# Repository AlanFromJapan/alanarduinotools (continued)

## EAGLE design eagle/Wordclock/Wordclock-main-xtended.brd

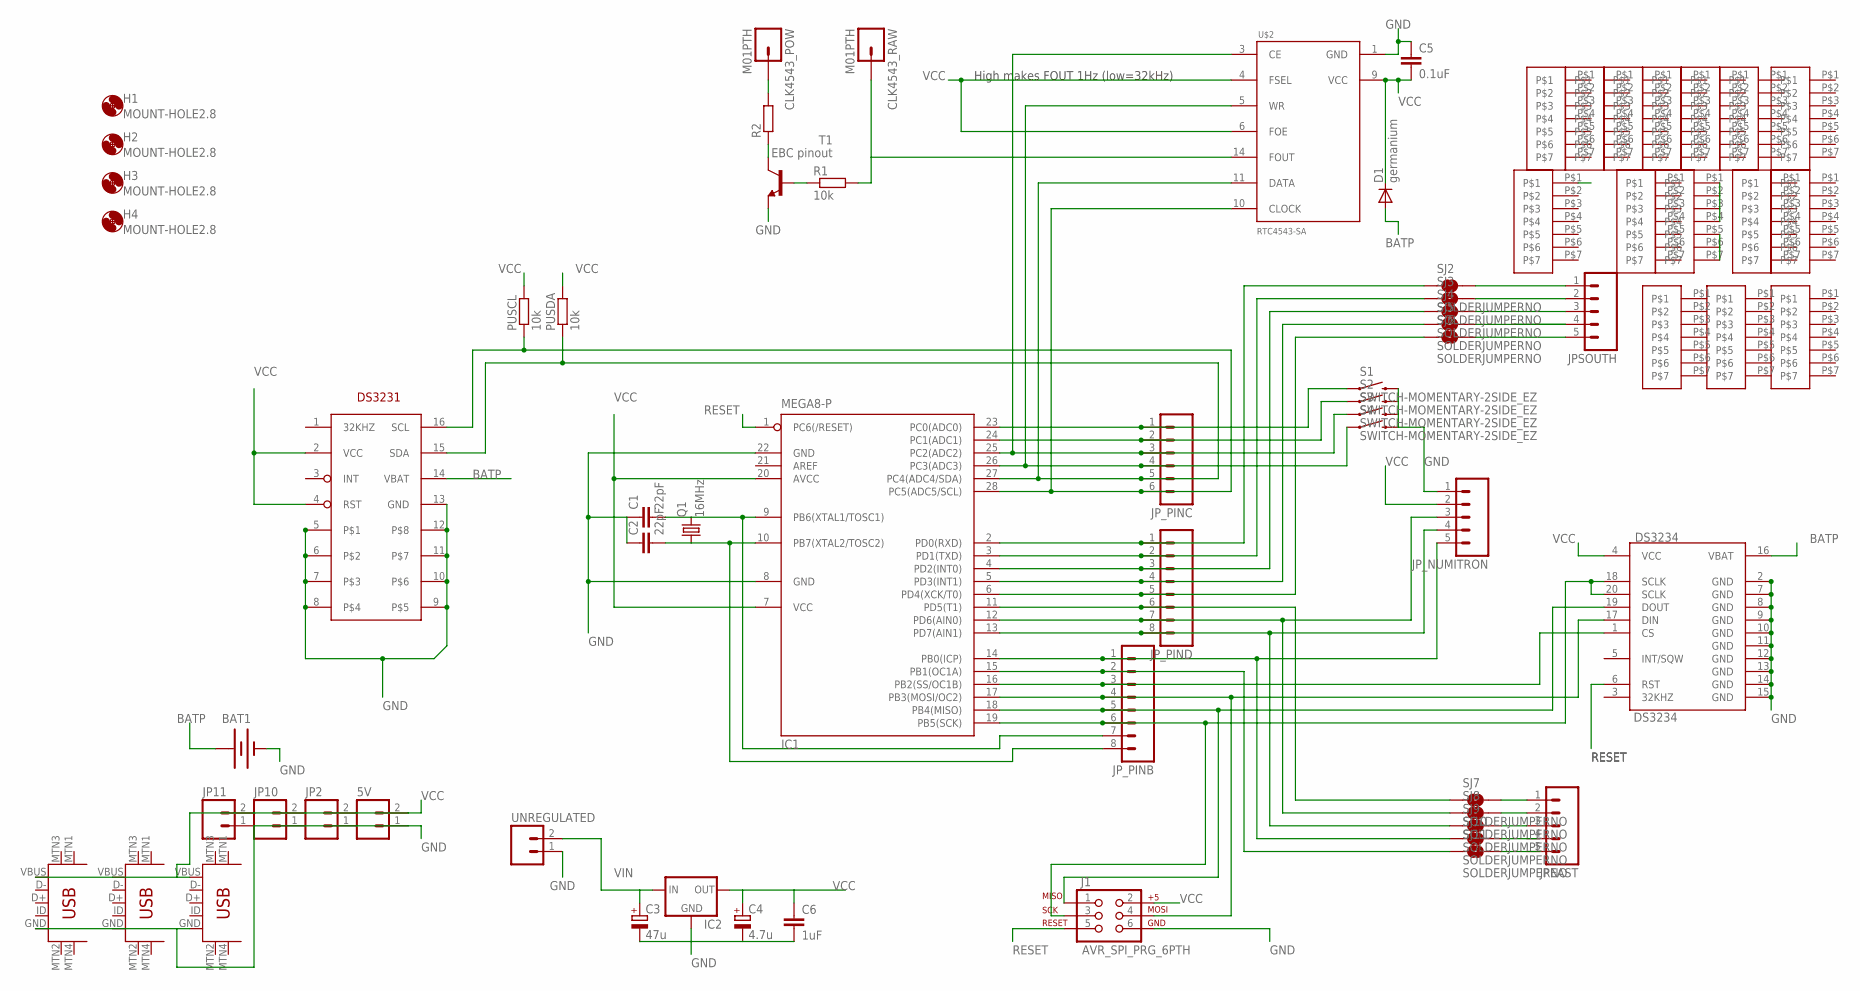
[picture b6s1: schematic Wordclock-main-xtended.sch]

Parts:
5V: M02PTH; 1X02
BAT1: BATTERY20PTH; BATTCOM_20MM_PTH
C1, C2: 22pF; C025-024X044
C3: 47u; E2,5-6E
C4: 4.7u; E2,5-6E
C5: 0.1uF; C025-024X044
C6: 1uF; C025-024X044
CLK4543_POW, CLK4543_RAW: M01PTH; 1X01
D1: germanium; D-7.5
DS3234: DS3234
H1, H2, H3, H4: MOUNT-HOLE2.8; 2,8
IC1: MEGA8-P; DIL28-3
IC2: V_REG_78XXSIDE; 78XXL
J1: AVR_SPI_PRG_6PTH; 2X3
JP1, JP3, JP4, JP5, JP6, JP7, JP8, JP9: M7_NOSILK
JP2: M02PTH; 1X02
JP10, JP11: M02PTH3; 1X02_LONGPADS
JPEAST: M05PTH; 1X05
JPSOUTH: M05PTH; 1X05
JP_NUMITRON: M05PTH; 1X05
JP_PINB: M081X08; 1X08
JP_PINC: M06SIP; 1X06
JP_PIND: M081X08; 1X08
PUSCL: 10k; 0204/5
PUSDA: 10k; 0204/5
Q1: 16MHz; HC49/S
R1: 10k; 0204/5
R2: R-EU_0204/5; 0204/5
S1, S2, S3, S4: SWITCH-MOMENTARY-2SIDE_EZ; TACTILE-PTH-SIDEEZ
SJ2, SJ3, SJ4, SJ5, SJ6, SJ7, SJ8, SJ9, SJ10, SJ11: SOLDERJUMPERNO; SJ_2S-NO
T1: EBC pinout; TO92-EBC
U$1: DS3231DS3231-SO16W; SO16W
U$2: RTC4543-SA; SOP14
U$3, U$4, U$5, U$6, U$8, U$9, U$10: M7_NOSILK
U$7, U$11, U$12: USB-MINIB-5PIN; USB-MINIB
UNREGULATED: M02PTH3; 1X02_LONGPADS

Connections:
BATP: BAT1.1 (+), D1.A, DS3234.16 (VBAT), U$1.14 (VBAT)
GND: 5V.1, BAT1.2 (-), C1.1, C2.1, C3.-, C4.-, C5.1, C6.2, DS3234.2 (GND), DS3234.7 (GND), DS3234.8 (GND), DS3234.9 (GND), DS3234.10 (GND), DS3234.11 (GND), DS3234.12 (GND), DS3234.13 (GND), DS3234.14 (GND), DS3234.15 (GND), IC1.8 (GND), IC1.22 (GND), IC2.GND, J1.6, JP2.1, JP10.1, JP11.1, JP_NUMITRON.1, S1.2, S2.2, S3.2, S4.2, T1.E, U$1.5, U$1.6, U$1.7, U$1.8, U$1.9, U$1.10, U$1.11, U$1.12, U$1.13 (GND), U$2.1 (GND), U$7.GND, U$8.P$1, U$8.P$2, U$8.P$3, U$8.P$4, U$11.GND, U$12.GND, UNREGULATED.1
unnamed: IC1.23 (PC0(ADC0)), JP_PINC.1, S1.1
unnamed: IC1.24 (PC1(ADC1)), JP_PINC.2, S2.1
unnamed: JPEAST.1, SJ7.2
unnamed: C1.2, IC1.9 (PB6(XTAL1/TOSC1)), JP_PINB.7, Q1.2
unnamed: C2.2, IC1.10 (PB7(XTAL2/TOSC2)), JP_PINB.8, Q1.1
unnamed: DS3234.1 (CS), IC1.16 (PB2(SS/OC1B)), JP_PINB.3
unnamed: IC1.25 (PC2(ADC2)), JP_PINC.3, S3.1, U$2.3 (CE)
unnamed: JPEAST.2, SJ8.2
unnamed: JPEAST.3, SJ9.2
unnamed: JPEAST.4, SJ10.2
unnamed: JPEAST.5, SJ11.2
unnamed: DS3234.18 (SCLK), DS3234.20 (SCLK), IC1.19 (PB5(SCK)), J1.3, JP_PINB.6
unnamed: DS3234.19 (DOUT), IC1.18 (PB4(MISO)), J1.1, JP_PINB.5
unnamed: DS3234.17 (DIN), IC1.17 (PB3(MOSI/OC2)), J1.4, JP_PINB.4
unnamed: JPSOUTH.1, SJ2.2
unnamed: JPSOUTH.2, SJ3.2
unnamed: JPSOUTH.3, SJ4.2
unnamed: JPSOUTH.4, SJ5.2
unnamed: JPSOUTH.5, SJ6.2
unnamed: IC1.2 (PD0(RXD)), JP_PIND.1, SJ2.1
unnamed: IC1.3 (PD1(TXD)), JP_PIND.2, SJ3.1
unnamed: IC1.4 (PD2(INT0)), JP_PIND.3, SJ4.1
unnamed: IC1.5 (PD3(INT1)), JP_PIND.4, SJ5.1
unnamed: IC1.6 (PD4(XCK/T0)), JP_PIND.5, SJ6.1
unnamed: IC1.15 (PB1(OC1A)), JP_PINB.2, SJ11.1
unnamed: IC1.14 (PB0(ICP)), JP_NUMITRON.5, JP_PINB.1, SJ10.1
unnamed: IC1.13 (PD7(AIN1)), JP_NUMITRON.4, JP_PIND.8, SJ9.1
unnamed: IC1.12 (PD6(AIN0)), JP_NUMITRON.3, JP_PIND.7, SJ8.1
unnamed: IC1.11 (PD5(T1)), JP_PIND.6, SJ7.1
unnamed: IC1.28 (PC5(ADC5/SCL)), JP_PINC.6, PUSCL.1, U$1.16 (SCL), U$2.10 (CLOCK)
unnamed: IC1.27 (PC4(ADC4/SDA)), JP_PINC.5, PUSDA.1, U$1.15 (SDA), U$2.11 (DATA)
unnamed: IC1.26 (PC3(ADC3)), JP_PINC.4, S4.1, U$2.5 (WR)
unnamed: CLK4543_RAW.1, R1.2, U$2.14 (FOUT)
unnamed: R1.1, T1.B
unnamed: R2.1, T1.C
unnamed: CLK4543_POW.1, R2.2
RESET: DS3234.6 (RST), IC1.1 (PC6(/RESET)), J1.5
VCC: 5V.2, C4.+, C5.2, C6.1, D1.C, DS3234.4 (VCC), IC1.7 (VCC), IC1.20 (AVCC), IC2.OUT, J1.2, JP2.2, JP10.2, JP11.2, JP_NUMITRON.2, PUSCL.2, PUSDA.2, U$1.2 (VCC), U$1.4 (RST), U$2.4 (FSEL), U$2.6 (FOE), U$2.9 (VCC), U$7.VBUS, U$8.P$5, U$8.P$6, U$8.P$7, U$10.P$1, U$11.VBUS, U$12.VBUS
VIN: C3.+, IC2.IN, UNREGULATED.2

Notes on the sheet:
High makes FOUT 1Hz (low=32kHz)

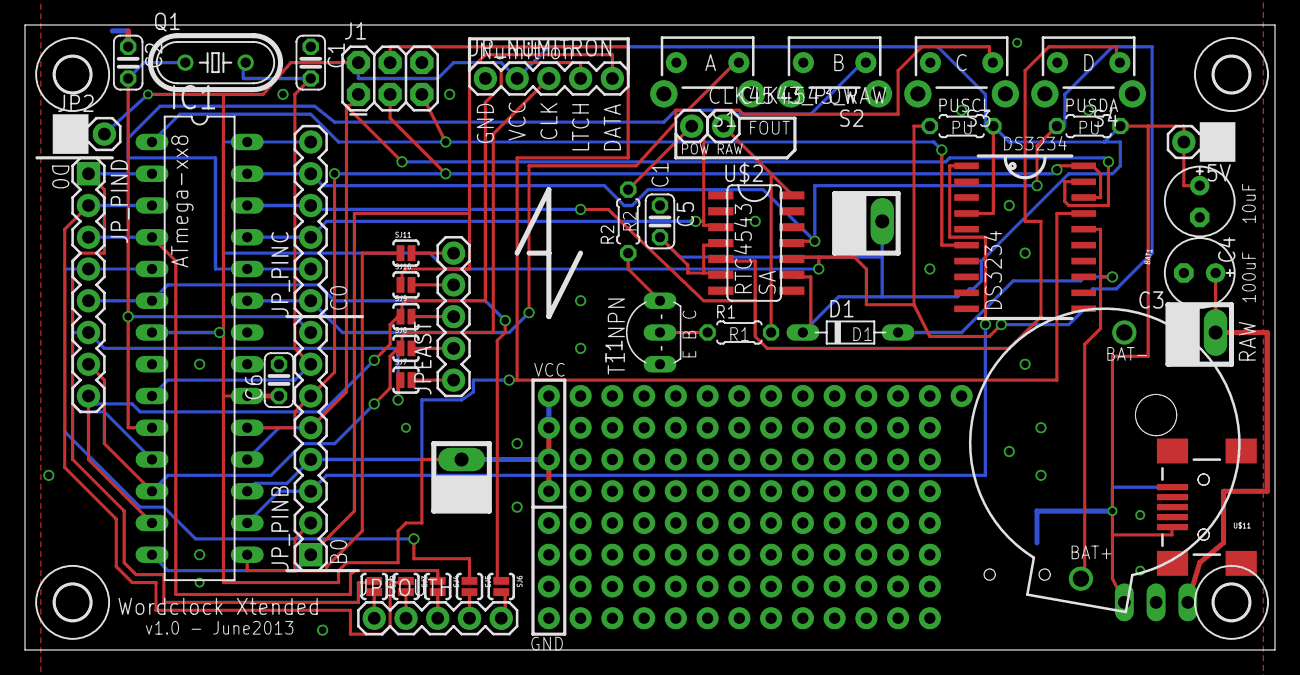
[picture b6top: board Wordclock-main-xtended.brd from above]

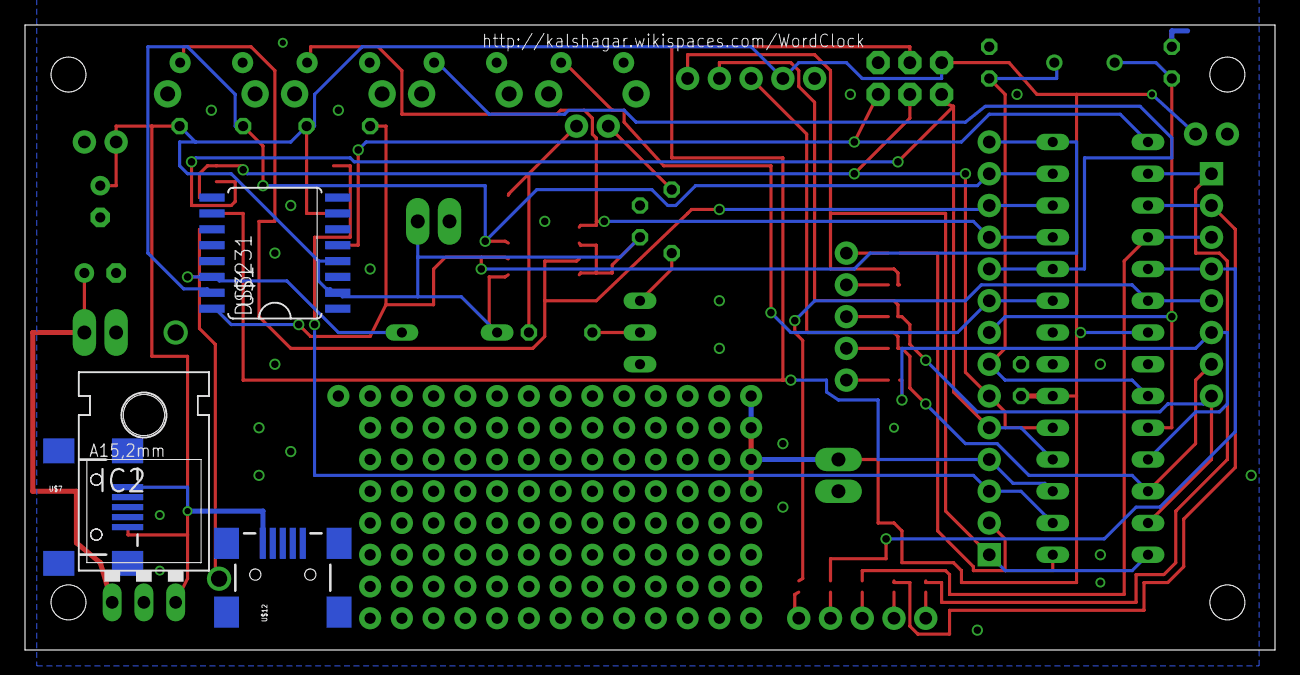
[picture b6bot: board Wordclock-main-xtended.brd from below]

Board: 2 copper layers, 100.0 x 50.0 mm, 69 parts (4 on the bottom side), 41 nets.

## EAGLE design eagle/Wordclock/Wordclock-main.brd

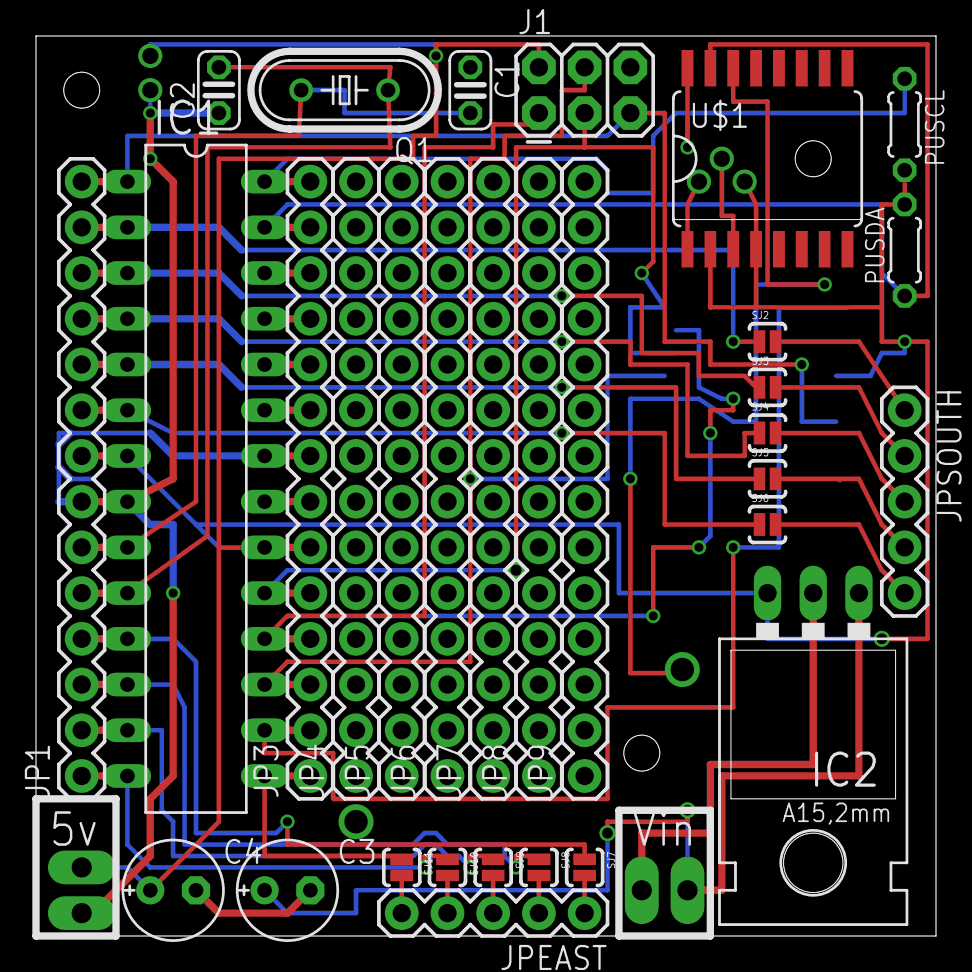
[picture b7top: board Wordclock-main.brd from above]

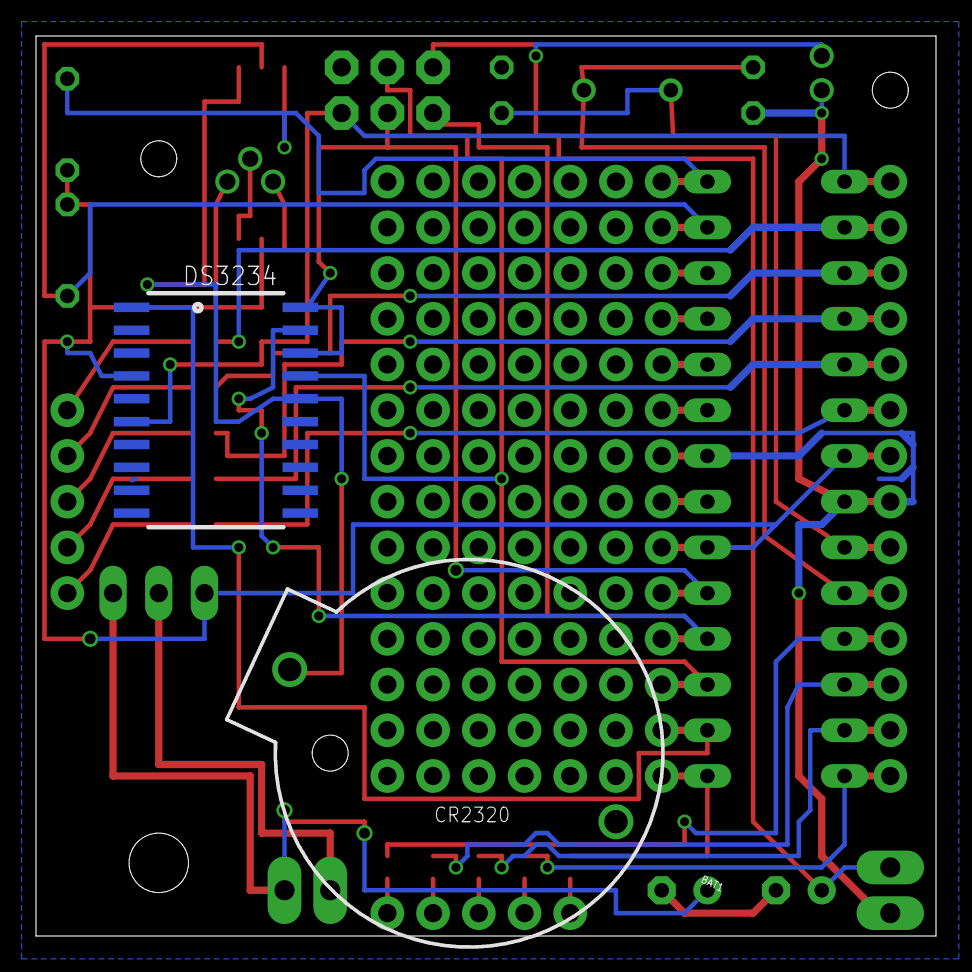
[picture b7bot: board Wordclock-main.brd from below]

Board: 2 copper layers, 50.0 x 50.0 mm, 35 parts (2 on the bottom side), 43 nets.

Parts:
5V: 1X02_LONGPADS
BAT1: BATTCOM_20MM_PTH
C1, C2: 22pF; C025-024X044
C3: 47u; E2,5-6E
C4: 4.7u; E2,5-6E
DS3234: DS3234
IC1: MEGA8-P; DIL28-3
IC2: 78XXL
J1: AVR_SPI_PRG_6PTH; 2X3
JP1, JP3, JP4, JP5, JP6, JP7, JP8, JP9: M14; 1X14
JPEAST: 1X05
JPSOUTH: 1X05
PUSCL: 10k; 0204/5
PUSDA: 10k; 0204/5
Q1: 16MHz; HC49/S
SJ2, SJ3, SJ4, SJ5, SJ6, SJ7, SJ8, SJ9, SJ10, SJ11: SOLDERJUMPERNO; SJ_2S-NO
U$1: DS3231; SO16W
UNREGULATED: 1X02_LONGPADS

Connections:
BATP: BAT1.1, DS3234.16, U$1.14
GND: 5V.1, BAT1.2, C1.1, C2.1, C3.-, C4.-, DS3234.2, DS3234.7, DS3234.8, DS3234.9, DS3234.10, DS3234.11, DS3234.12, DS3234.13, DS3234.14, DS3234.15, IC1.8, IC1.22, IC2.GND, J1.6, JP1.7, JP3.8, UNREGULATED.1
unnamed: JPEAST.1, SJ7.2
unnamed: C1.2, IC1.9, JP1.6, Q1.2
unnamed: C2.2, IC1.10, JP1.5, Q1.1
unnamed: IC1.16, JP3.2
unnamed: JPEAST.2, SJ8.2
unnamed: JPEAST.3, SJ9.2
unnamed: JPEAST.4, SJ10.2
unnamed: JPEAST.5, SJ11.2
unnamed: DS3234.18, DS3234.20, IC1.19, J1.3, JP3.5
unnamed: DS3234.17, IC1.17, J1.4, JP3.3
unnamed: JPSOUTH.1, SJ2.2
unnamed: JPSOUTH.2, SJ3.2
unnamed: JPSOUTH.3, SJ4.2
unnamed: JPSOUTH.4, SJ5.2
unnamed: JPSOUTH.5, SJ6.2
unnamed: IC1.2, JP1.13, SJ2.1
unnamed: IC1.3, JP1.12, SJ3.1
unnamed: IC1.4, JP1.11, SJ4.1
unnamed: IC1.5, JP1.10, SJ5.1
unnamed: IC1.6, JP1.9, SJ6.1
unnamed: IC1.15, JP3.1, SJ11.1
unnamed: IC1.14, JP1.1, SJ10.1
unnamed: IC1.13, JP1.2, SJ9.1
unnamed: IC1.12, JP1.3, SJ8.1
unnamed: IC1.11, JP1.4, SJ7.1
unnamed: IC1.28, JP3.14, PUSCL.1
unnamed: IC1.27, JP3.13, PUSDA.1, U$1.15
RESET: DS3234.6, IC1.1, J1.5, JP1.14
S$2: IC1.26, JP3.12
S$3: IC1.25, JP3.11
S$4: IC1.24, JP3.10
S$5: IC1.23, JP3.9
S$6: IC1.21, JP3.7
S$7: U$1.12, U$1.13
S$8: U$1.7, U$1.8
S$9: U$1.5, U$1.6
S$11: U$1.9, U$1.10, U$1.11
S$12: U$1.2, U$1.4
S$13: DS3234.19, IC1.18, J1.1, JP3.4
VCC: 5V.2, C4.+, DS3234.4, IC1.7, IC1.20, IC2.OUT, J1.2, JP1.8, JP3.6, PUSCL.2, PUSDA.2
VIN: C3.+, IC2.IN, UNREGULATED.2
